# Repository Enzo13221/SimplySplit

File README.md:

# SimplySplit
This is my low profile split keyboard. I made this because I really wanted to make a keyboard but also didnt want it to be too simple. This is why I made a bluetooth split keyboard. Because of it's small form factor it can "fit" into your pocket. This is useful as I really enjoy using my old RasPi on the go and a bt keyboard is realy useful.

## Images

(If you noticed that the connector for the Battery is being clipped by the top plate I decided to not use the connector but leave the footprint there as an option)

# Firmware can be found here

https://github.com/Enzo13221/ZMK-Config-SimplySplit 

# BOM
| Item            | Description        | Quantity | Unit price | Total price | Price + tax | Running total | Link       |
| --------------- | ------------------ | -------- | ---------- | ----------- | ----------- | ------------- | ---------- |
| Keycaps         | CFX, White         | 40       | $0.33      | $13.07      | $14.77      | $14.77        | [AliExpress](https://www.aliexpress.us/item/3256810199199272.html?spm=a2g0o.detail.pcDetailBottomMoreOtherSeller.23.51667HnN7HnNaF&gps-id=pcDetailBottomMoreOtherSeller&scm=1007.40050.354490.0&scm_id=1007.40050.354490.0&scm-url=1007.40050.354490.0&pvid=384d1b43-ab82-45ca-9332-caee7cd0b6ae&_t=gps-id:pcDetailBottomMoreOtherSeller,scm-url:1007.40050.354490.0,pvid:384d1b43-ab82-45ca-9332-caee7cd0b6ae,tpp_buckets:668%232846%238107%231934&pdp_ext_f=%7B"order"%3A"22"%2C"eval"%3A"1"%2C"sceneId"%3A"30050"%2C"fromPage"%3A"recommend"%7D&pdp_npi=6%40dis%21USD%219.70%210.99%21%21%219.70%210.99%21%402101ea8c17712834864303402ea509%2112000052228852471%21rec%21US%21%21ABXZ%211%210%21n_tag%3A-29910%3Bd%3A5299cee1%3Bm03_new_user%3A-29895%3BpisId%3A5000000197847450&utparam-url=scene%3ApcDetailBottomMoreOtherSeller%7Cquery_from%3A%7Cx_object_id%3A1005010385514024%7C_p_origin_prod%3A) |
| Switches        | Choc v1 brown      | 40       | $0.74      | $14.87      | $16.80      | $31.57        | [AliExpress](https://www.aliexpress.us/item/3256806486085031.html?spm=a2g0o.productlist.main.10.41f013a7iUGzO1&algo_pvid=29c271cb-d14e-451b-9722-29b87397267c&algo_exp_id=29c271cb-d14e-451b-9722-29b87397267c-9&pdp_ext_f=%7B"order"%3A"97"%2C"eval"%3A"1"%2C"fromPage"%3A"search"%7D&pdp_npi=6%40dis%21USD%216.92%216.92%21%21%2147.48%2147.48%21%402103128817712830262832957ee54e%2112000037979106609%21sea%21US%210%21ABX%211%210%21n_tag%3A-29910%3Bd%3A5299cee1%3Bm03_new_user%3A-29895&curPageLogUid=fiXY8vuLofNm&utparam-url=scene%3Asearch%7Cquery_from%3A%7Cx_object_id%3A1005006672399783%7C_p_origin_prod%3A) |
| Batteries       | 3.7V 200mAh        | 2        | $2.84      | $5.68       | $6.42       | $37.99        | [AliExpress](https://www.aliexpress.us/item/2251832643018973.html?spm=a2g0o.detail.pcDetailTopMoreOtherSeller.4.2706ETrhETrhlN&gps-id=pcDetailTopMoreOtherSeller&scm=1007.40050.354490.0&scm_id=1007.40050.354490.0&scm-url=1007.40050.354490.0&pvid=02574686-c7bf-467c-94c4-5f7aa57118c0&_t=gps-id:pcDetailTopMoreOtherSeller,scm-url:1007.40050.354490.0,pvid:02574686-c7bf-467c-94c4-5f7aa57118c0,tpp_buckets:668%232846%238111%231996&isseo=y&pdp_ext_f=%7B"order"%3A"116"%2C"eval"%3A"1"%2C"sceneId"%3A"30050"%2C"fromPage"%3A"recommend"%7D&pdp_npi=6%40dis%21USD%212.84%212.84%21%21%212.84%212.84%21%40210328df17712797568823146e484c%2112000040902843221%21rec%21US%21%21ABX%211%210%21n_tag%3A-29910%3Bd%3A5299cee1%3Bm03_new_user%3A-29895&utparam-url=scene%3ApcDetailTopMoreOtherSeller%7Cquery_from%3A%7Cx_object_id%3A32829333725%7C_p_origin_prod%3A)  |
| Molex Connector | WM1742-ND          | 2        | $0.45      | $0.90       | $1.02       | $39.01        | [DigiKey](https://www.digikey.ca/en/products/detail/molex/0530480210/242864)    |
| Resistor        | MFR-25FBF52-806K   | 2        | $0.14      | $0.28       | $0.32       | $39.32        | [DigiKey](https://www.digikey.ca/en/products/detail/yageo/MFR-25FBF52-806K/13696)    |
| Resistor        | HVR3700002004FR500 | 2        | $0.58      | $1.16       | $1.31       | $40.63        | [DigiKey](https://www.digikey.ca/en/products/detail/vishay-beyschlag-draloric-bc-components/HVR3700002004FR500/719532)    |
| Diode           | 1N4148W            | 45       | $0.19      | $1.89       | $2.14       | $42.77        | [DigiKey](https://www.digikey.ca/en/products/detail/smc-diode-solutions/1N4148W/6022450)   |
| PCB+Top plate   | See attached image | 1        | $42.79     | $42.79      | $42.79      | $85.56       | N/A        |
| Bolts           | M3x20mm            | 20       | $0.18      | $3.54       | $4.00       | $89.56       | [AliExpress](https://www.aliexpress.us/item/3256807895942562.html?spm=a2g0o.productlist.main.17.5ab26bba9gkouK&algo_pvid=9569f8b8-50c7-4709-bb61-aa0e50691b59&algo_exp_id=9569f8b8-50c7-4709-bb61-aa0e50691b59-16&pdp_ext_f=%7B"order"%3A"815"%2C"eval"%3A"1"%2C"fromPage"%3A"search"%7D&pdp_npi=6%40dis%21USD%211.64%210.99%21%21%211.64%210.99%21%402101e81117712966712334141eaf0b%2112000043609478511%21sea%21US%210%21ABX%211%210%21n_tag%3A-29910%3Bd%3A5299cee1%3Bm03_new_user%3A-29895%3BpisId%3A5000000198352206&curPageLogUid=pqj3T9RK0P7g&utparam-url=scene%3Asearch%7Cquery_from%3A%7Cx_object_id%3A1005008082257314%7C_p_origin_prod%3A) |
| Spacers         | M3x6mmx1mm         | 200      | $0.02      | $2.21       | $2.50       | $92.06       | [AliExpress](https://www.aliexpress.us/item/3256807407806741.html?spm=a2g0o.productlist.main.1.65091593KQNbL0&algo_pvid=b8acf6cb-9c4f-45eb-a65f-3304e9bf4beb&algo_exp_id=b8acf6cb-9c4f-45eb-a65f-3304e9bf4beb-0&pdp_ext_f=%7B"order"%3A"32"%2C"eval"%3A"1"%2C"fromPage"%3A"search"%7D&pdp_npi=6%40dis%21USD%212.21%210.99%21%21%2115.17%216.80%21%402103212b17712919601903092e4830%2112000041427681765%21sea%21US%210%21ABX%211%210%21n_tag%3A-29910%3Bd%3A5299cee1%3Bm03_new_user%3A-29895%3BpisId%3A5000000198352206&curPageLogUid=T75qFSRd0QTp&utparam-url=scene%3Asearch%7Cquery_from%3A%7Cx_object_id%3A1005007594121493%7C_p_origin_prod%3A) |

[BOM](https://docs.google.com/spreadsheets/d/1cfBUe_hsh4m0duevO8yELbZ5TltpPVcU9Z1VGttN0Io/edit?usp=sharing)

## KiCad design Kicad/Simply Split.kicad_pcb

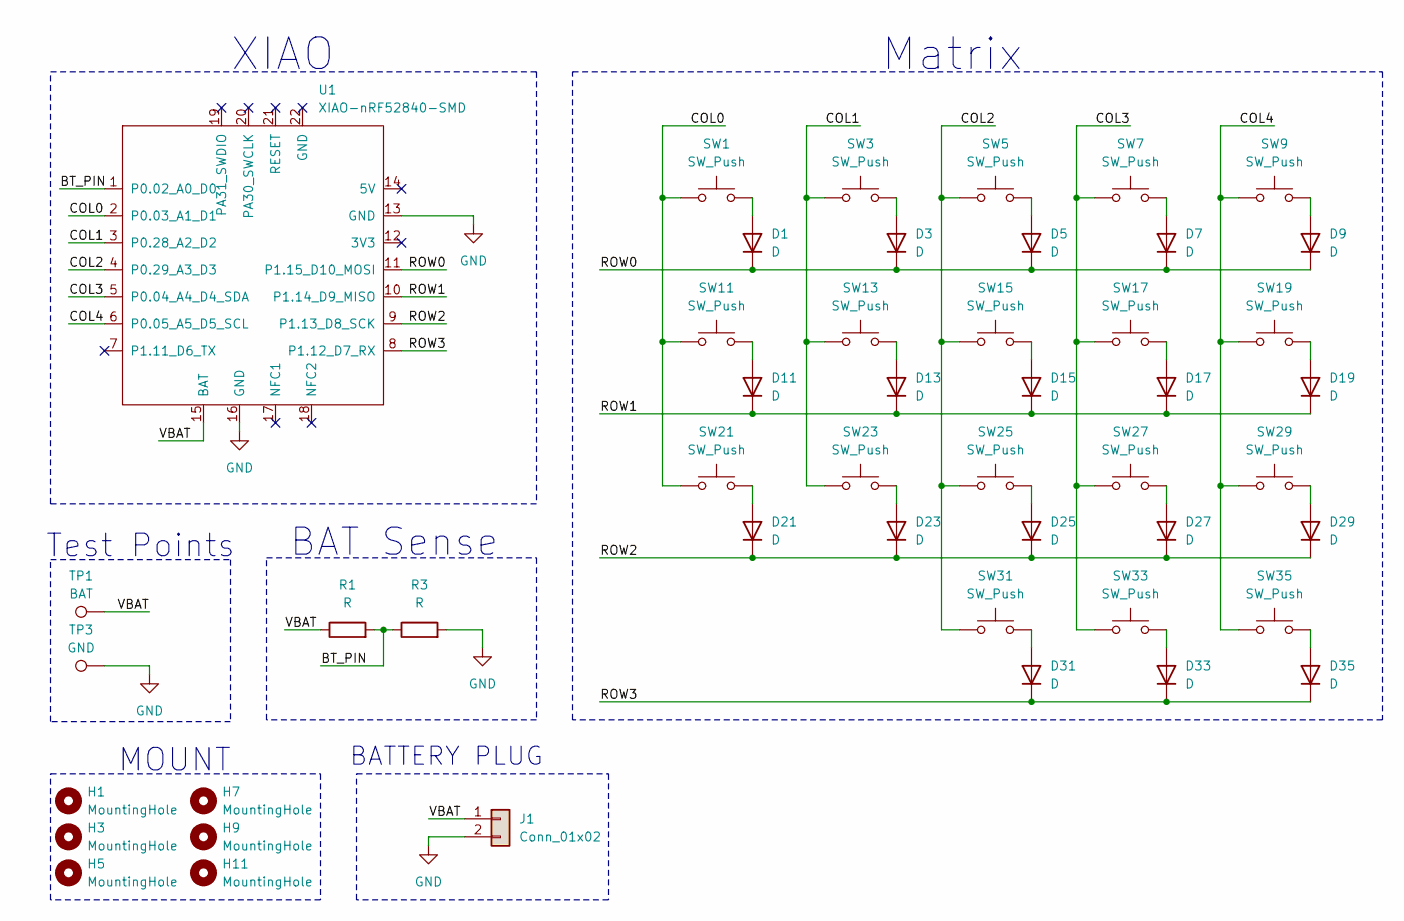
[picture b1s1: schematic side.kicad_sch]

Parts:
D1, D3, D5, D7, D9, D11, D13, D15, D17, D19, D21, D23, D25, D27, D29, D31, D33, D35: D; diode123reverse
H1, H3, H5, H7, H9, H11: MountingHole; MountingHole_3.2mm_M3
J1: Conn_01x02; Molex_PicoBlade_53048-0210_1x02_P1.25mm_Horizontal
R1, R3: R; R_0805_2012Metric
SW1, SW3, SW5, SW7, SW9, SW11, SW13, SW15, SW17, SW19, SW21, SW23, SW25, SW27, SW29, SW31, SW33, SW35: SW_Push; SW_PG1350_reversible
TP1: BAT; TestPoint_Pad_D2.5mm
TP3: GND; TestPoint_Pad_D2.5mm
U1: XIAO-nRF52840-SMD; modified-XIAO-nRF52840-SMD (1)

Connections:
/Left/BT_PIN: R1.2, R3.1, U1.1 (P0.02_A0_D0)
/Left/COL0: SW1.1, SW11.1, SW21.1, U1.2 (P0.03_A1_D1)
/Left/COL1: SW3.1, SW13.1, SW23.1, U1.3 (P0.28_A2_D2)
/Left/COL2: SW5.1, SW15.1, SW25.1, SW31.1, U1.4 (P0.29_A3_D3)
/Left/COL3: SW7.1, SW17.1, SW27.1, SW33.1, U1.5 (P0.04_A4_D4_SDA)
/Left/COL4: SW9.1, SW19.1, SW29.1, SW35.1, U1.6 (P0.05_A5_D5_SCL)
/Left/ROW0: D1.1 (K), D3.1 (K), D5.1 (K), D7.1 (K), D9.1 (K), U1.11 (P1.15_D10_MOSI)
/Left/ROW1: D11.1 (K), D13.1 (K), D15.1 (K), D17.1 (K), D19.1 (K), U1.10 (P1.14_D9_MISO)
/Left/ROW2: D21.1 (K), D23.1 (K), D25.1 (K), D27.1 (K), D29.1 (K), U1.9 (P1.13_D8_SCK)
/Left/ROW3: D31.1 (K), D33.1 (K), D35.1 (K), U1.8 (P1.12_D7_RX)
/Left/VBAT: J1.1, R1.1, TP1.1, U1.15 (BAT)
GND: J1.2, R3.2, TP3.1, U1.13 (GND), U1.16 (GND)
unnamed: D1.2 (A), SW1.2
unnamed: D3.2 (A), SW3.2
unnamed: D5.2 (A), SW5.2
unnamed: D7.2 (A), SW7.2
unnamed: D9.2 (A), SW9.2
unnamed: D11.2 (A), SW11.2
unnamed: D13.2 (A), SW13.2
unnamed: D15.2 (A), SW15.2
unnamed: D17.2 (A), SW17.2
unnamed: D19.2 (A), SW19.2
unnamed: D21.2 (A), SW21.2
unnamed: D23.2 (A), SW23.2
unnamed: D25.2 (A), SW25.2
unnamed: D27.2 (A), SW27.2
unnamed: D29.2 (A), SW29.2
unnamed: D31.2 (A), SW31.2
unnamed: D33.2 (A), SW33.2
unnamed: D35.2 (A), SW35.2

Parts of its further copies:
H2, H4, H8: MountingHole; MountingHole_3.2mm_M3

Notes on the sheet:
BATTERY PLUG
BAT Sense
Matrix
MOUNT
XIAO
Test Points

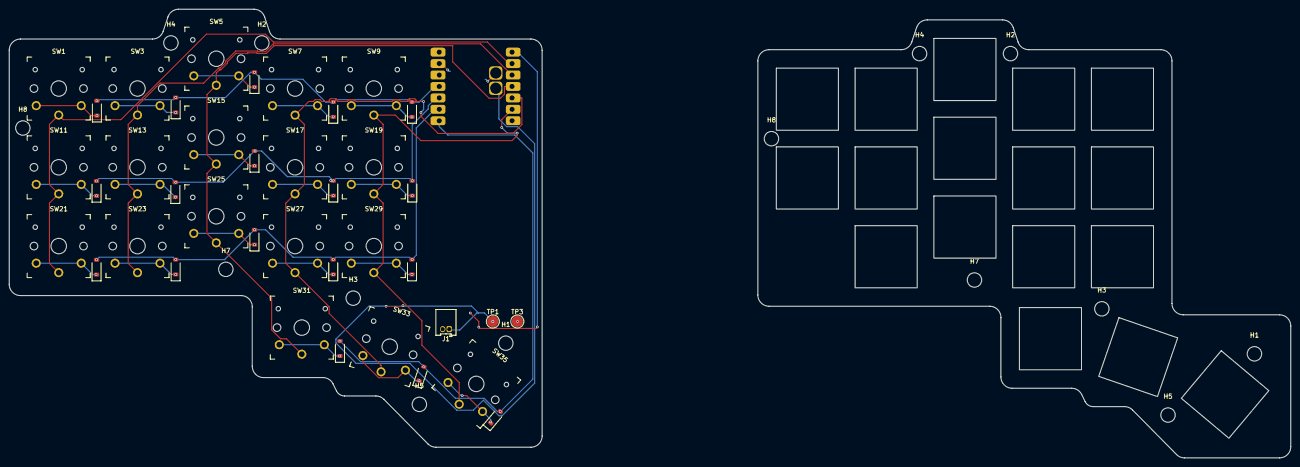
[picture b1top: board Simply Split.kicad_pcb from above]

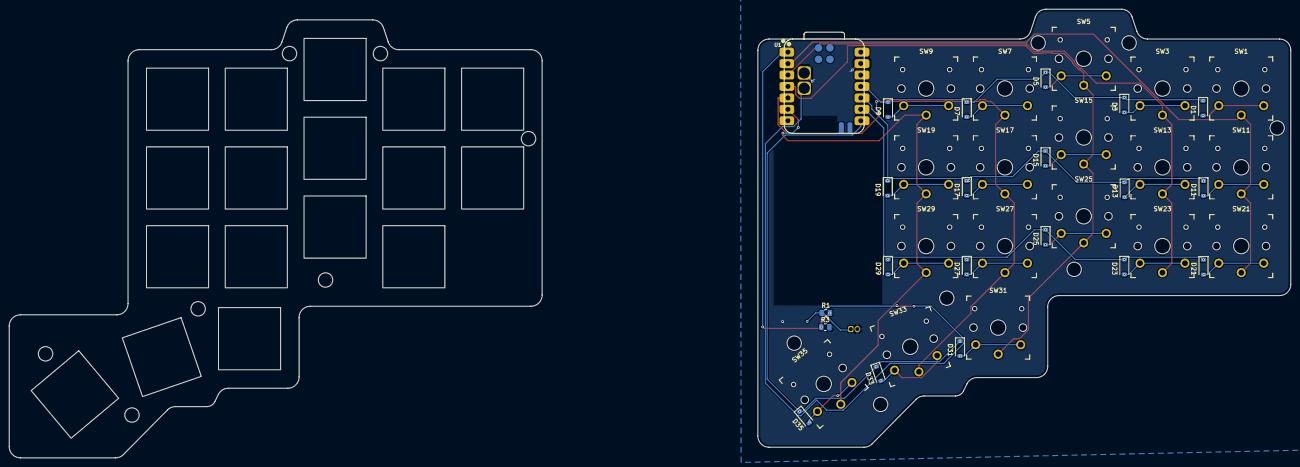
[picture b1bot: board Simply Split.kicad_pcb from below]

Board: 2 copper layers, 284.7 x 99.7 mm, 56 parts (21 on the bottom side), 30 nets.

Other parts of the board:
H1#2, H2#2, H3#2, H4#2, H5#2, H7#2, H8#2: MountingHole; MountingHole_3.2mm_M3

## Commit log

2026-02-17 Added BOM
2026-02-17 Fix BOM
2026-02-17 First big commit
2026-02-17 added spacers
2026-02-17 Moved BOM to root
2026-02-17 Fixed repo as requested
2026-02-17 Fix image links and add more images in README
2026-02-17 Added .STEP
2026-02-18 Added file
2026-02-18 Fized link and added image of layout
2026-02-23 Updates to prices
2026-03-29 Case created
2026-03-31 Fixed case file
2026-03-31 UPD for submit
2026-03-31 Fixed assembled
2026-04-02 Payment n lil changes
